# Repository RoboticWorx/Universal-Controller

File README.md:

# Universal_Controller
Files for my Universal Remote Controller project. 

***(Remember, you can download anything you'd like for yourself but you CAN'T sell or redistribute it. All my work is licensed, thanks!)***

Be sure to go to www.roboticworx.io for detailed tutorials on a variety of projects! Thanks for reading and happy making!

Best regards, 
Justin

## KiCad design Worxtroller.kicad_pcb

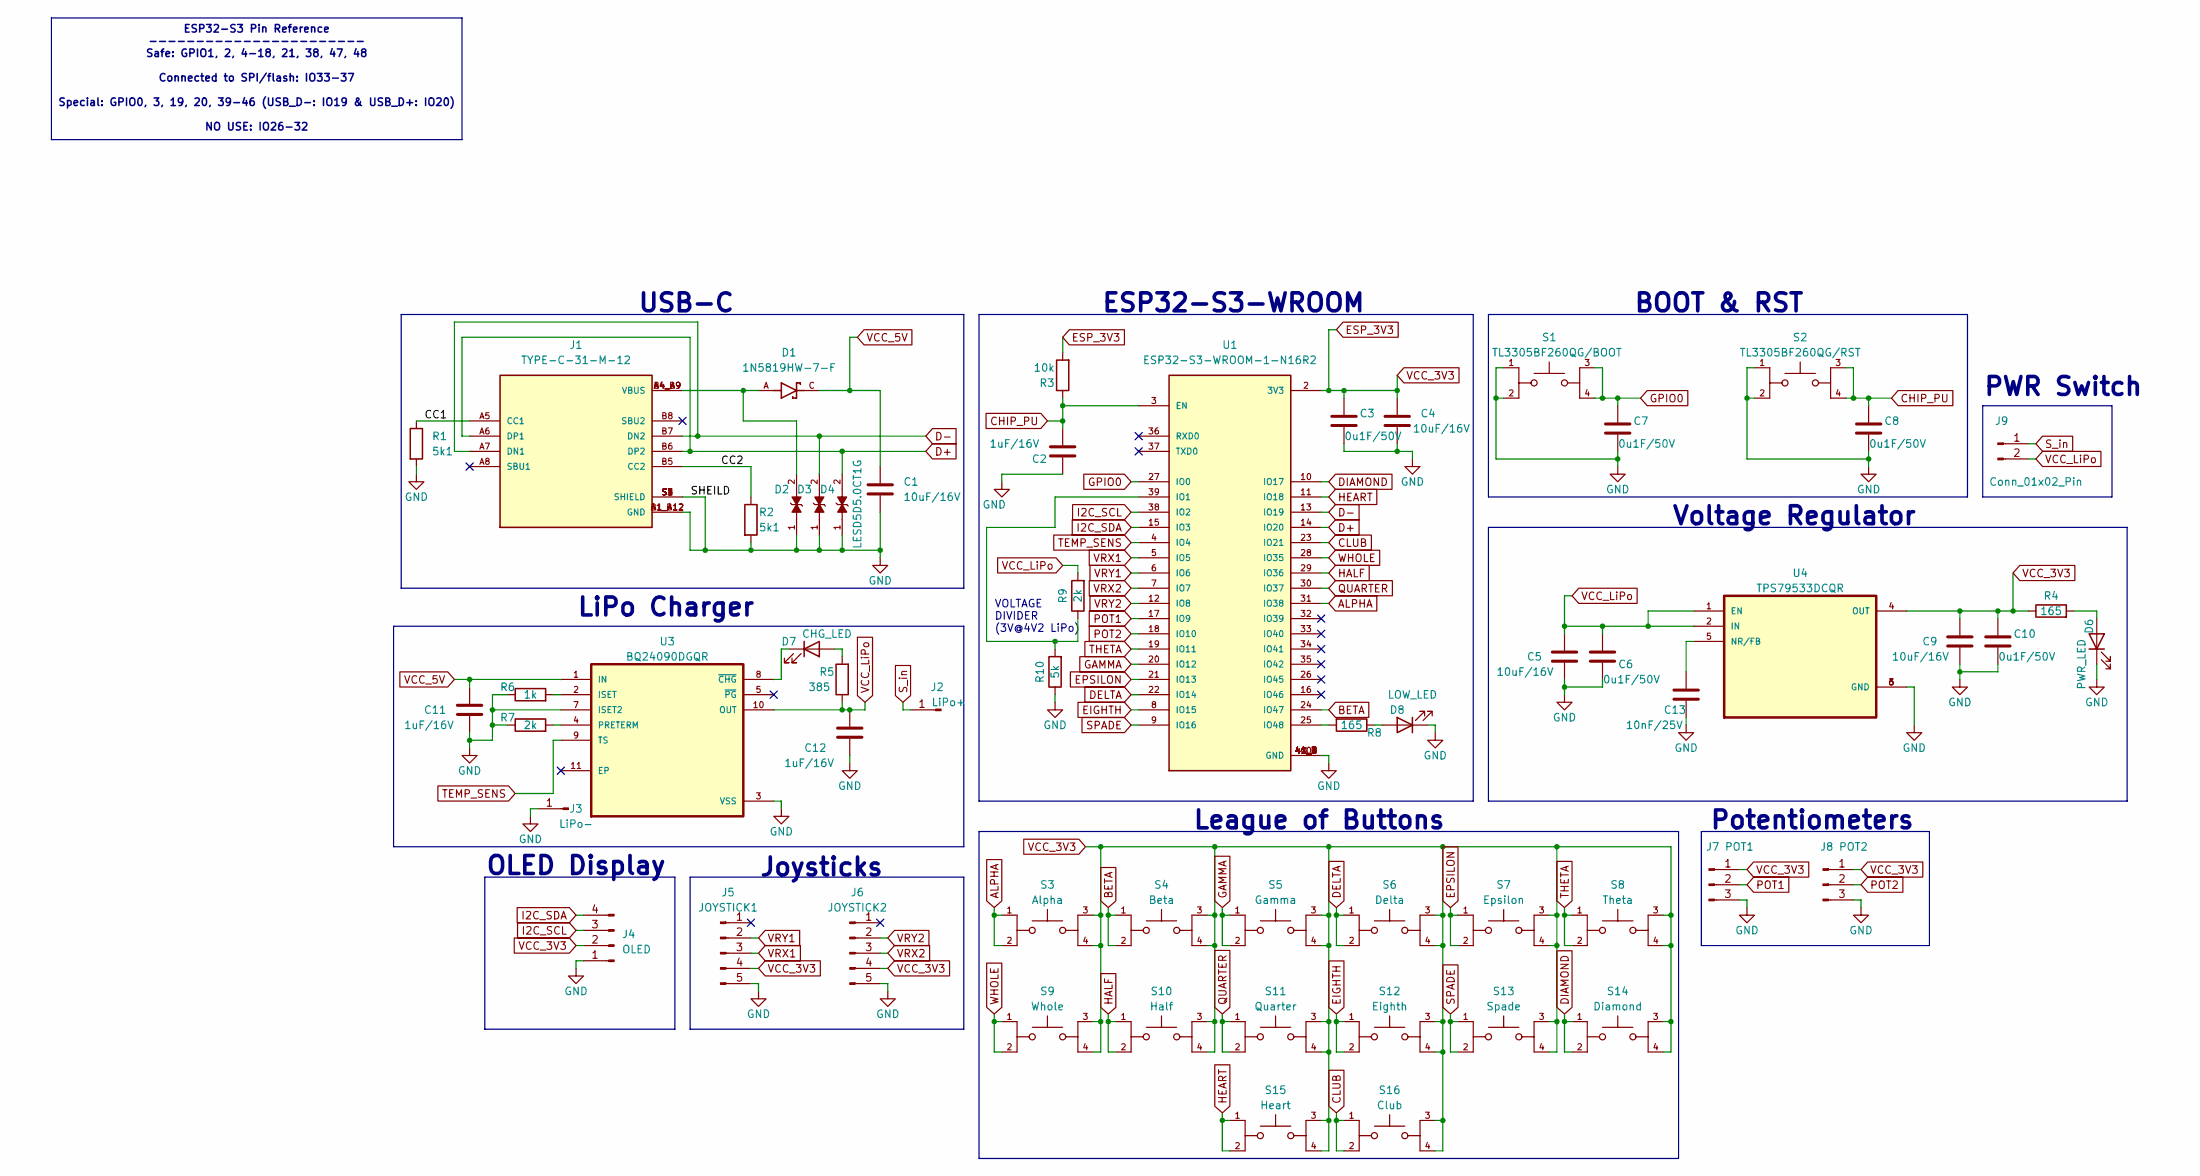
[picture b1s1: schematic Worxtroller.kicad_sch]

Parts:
C1, C4, C5, C9: 10uF/16V; C_0805_2012Metric_Pad1.18x1.45mm_HandSolder
C2, C11, C12: 1uF/16V; C_0603_1608Metric_Pad1.08x0.95mm_HandSolder
C3, C6, C7, C8, C10: 0u1F/50V; C_0201_0603Metric_Pad0.64x0.40mm_HandSolder
C13: 10nF/25V; C_0201_0603Metric_Pad0.64x0.40mm_HandSolder
D1: 1N5819HW-7-F; SOD3715X145N; PARTREV 18-2
D2, D3, D4: LESD5D5.0CT1G; TVS_LESD5D5.0CT1G; PARTREV O
D6: PWR_LED; LED_D3.0mm
D7: CHG_LED; LED_D3.0mm
D8: LOW_LED; LED_D3.0mm
J1: TYPE-C-31-M-12; HRO_TYPE-C-31-M-12; PARTREV 2020.12.08
J2: LiPo+; PinHeader_1x01_P2.54mm_Vertical
J3: LiPo-; PinHeader_1x01_P2.54mm_Vertical
J4: OLED; PinHeader_1x04_P2.54mm_Vertical
J5: JOYSTICK1; PinHeader_1x05_P2.54mm_Vertical
J6: JOYSTICK2; PinHeader_1x05_P2.54mm_Vertical
J7: POT1; PinHeader_1x03_P2.54mm_Vertical
J8: POT2; PinHeader_1x03_P2.54mm_Vertical
J9: Conn_01x02_Pin; PinHeader_1x02_P2.54mm_Vertical
R1, R2: 5k1; R_0805_2012Metric_Pad1.20x1.40mm_HandSolder
R3: 10k; R_0805_2012Metric_Pad1.20x1.40mm_HandSolder
R4, R8: 165; R_0603_1608Metric_Pad0.98x0.95mm_HandSolder
R5: 385; R_0603_1608Metric_Pad0.98x0.95mm_HandSolder
R6: 1k; R_0805_2012Metric_Pad1.20x1.40mm_HandSolder
R7, R9: 2k; R_0805_2012Metric_Pad1.20x1.40mm_HandSolder
R10: 5k; R_0805_2012Metric_Pad1.20x1.40mm_HandSolder
S1: TL3305BF260QG/BOOT; SW_TL3305BF260QG; PARTREV C
S2: TL3305BF260QG/RST; SW_TL3305BF260QG; PARTREV C
S3: Alpha; SW_TL3305BF260QG; PARTREV C
S4: Beta; SW_TL3305BF260QG; PARTREV C
S5: Gamma; SW_TL3305BF260QG; PARTREV C
S6: Delta; SW_TL3305BF260QG; PARTREV C
S7: Epsilon; SW_TL3305BF260QG; PARTREV C
S8: Theta; SW_TL3305BF260QG; PARTREV C
S9: Whole; SW_TL3305BF260QG; PARTREV C
S10: Half; SW_TL3305BF260QG; PARTREV C
S11: Quarter; SW_TL3305BF260QG; PARTREV C
S12: Eighth; SW_TL3305BF260QG; PARTREV C
S13: Spade; SW_TL3305BF260QG; PARTREV C
S14: Diamond; SW_TL3305BF260QG; PARTREV C
S15: Heart; SW_TL3305BF260QG; PARTREV C
S16: Club; SW_TL3305BF260QG; PARTREV C
U1: ESP32-S3-WROOM-1-N16R2; XCVR_ESP32-S3-WROOM-1-N16R2; PARTREV v1.0
U3: BQ24090DGQR; IC_XTR111AIDGQR
U4: TPS79533DCQR; SOT127P706X180-6N

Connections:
/CC1: J1.A5 (CC1), R1.1
/CC2: J1.B5 (CC2), R2.1
ALPHA: S3.1, S3.2, U1.31 (IO38)
BETA: S4.1, S4.2, U1.24 (IO47)
CHIP_PU: C2.2, C8.1, R3.1, S2.3, S2.4, U1.3 (EN)
CLUB: S16.1, S16.2, U1.23 (IO21)
D+: D4.2, J1.A6 (DP1), J1.B6 (DP2), U1.14 (IO20)
D-: D3.2, J1.A7 (DN1), J1.B7 (DN2), U1.13 (IO19)
DELTA: S6.1, S6.2, U1.22 (IO14)
DIAMOND: S14.1, S14.2, U1.10 (IO17)
EIGHTH: S12.1, S12.2, U1.8 (IO15)
EPSILON: S7.1, S7.2, U1.21 (IO13)
ESP_3V3: C3.1, C4.1, C9.1, C10.1, J4.2, J5.4, J6.4, J7.1, J8.1, R3.2, R4.1, S3.3, S3.4, S4.3, S4.4, S5.3, S5.4, S6.3, S6.4, S7.3, S7.4, S8.3, S8.4, S9.3, S9.4, S10.3, S10.4, S11.3, S11.4, S12.3, S12.4, S13.3, S13.4, S14.3, S14.4, S15.3, S15.4, S16.3, S16.4, U1.2 (3V3), U4.4 (OUT)
GAMMA: S5.1, S5.2, U1.20 (IO12)
GPIO0: C7.1, S1.3, S1.4, U1.27 (IO0)
HALF: S10.1, S10.2, U1.29 (IO36)
HEART: S15.1, S15.2, U1.11 (IO18)
I2C_SCL: J4.3, U1.38 (IO2)
I2C_SDA: J4.4, U1.15 (IO3)
unnamed: D1.A, D2.2, J1.A4_B9 (VBUS), J1.B4_A9 (VBUS)
unnamed: D6.2 (A), R4.2
unnamed: D7.2 (A), R5.2
unnamed: D7.1 (K), U3.8 (~CHG)
unnamed: D8.2 (A), R8.1
unnamed: R9.1, R10.2, U1.39 (IO1)
unnamed: R8.2, U1.25 (IO48)
unnamed: R6.2, U3.2 (ISET)
unnamed: R7.2, U3.4 (PRETERM)
unnamed: C13.1, U4.5 (NR/FB)
POT1: J7.2, U1.17 (IO9)
POT2: J8.2, U1.18 (IO10)
QUARTER: S11.1, S11.2, U1.30 (IO37)
SENSE: U1.4 (IO4), U3.9 (TS)
SPADE: S13.1, S13.2, U1.9 (IO16)
S_in: J2.1, J9.1
TEMP_SENS: C1.2, C2.1, C3.2, C4.2, C5.2, C6.2, C7.2, C8.2, C9.2, C10.2, C11.1, C12.1, C13.2, D2.1, D3.1, D4.1, D6.1 (K), D8.1 (K), J1.A1_B12 (GND), J1.B1_A12 (GND), J1.S1 (SHIELD), J1.S2 (SHIELD), J1.S3 (SHIELD), J1.S4 (SHIELD), J3.1, J4.1, J5.5, J6.5, J7.3, J8.3, R1.2, R2.2, R6.1, R7.1, R10.1, S1.1, S1.2, S2.1, S2.2, U1.1 (GND), U1.40 (GND), U1.41_1 (GND), U1.41_2 (GND), U1.41_3 (GND), U1.41_4 (GND), U1.41_5 (GND), U1.41_6 (GND), U1.41_7 (GND), U1.41_8 (GND), U1.41_9 (GND), U1.41_10, U1.41_11, U1.41_12, U1.41_13, U1.41_14, U1.41_15, U1.41_16, U1.41_17, U1.41_18, U1.41_19, U1.41_20, U1.41_21, U3.3 (VSS), U3.7 (ISET2), U3.11 (EP), U3.12, U3.13, U3.14, U3.15, U3.16, U4.3 (GND), U4.6 (GND)
THETA: S8.1, S8.2, U1.19 (IO11)
VCC_5V: C1.1, C11.2, D1.C, U3.1 (IN)
VCC_LiPo: C5.1, C6.1, C12.2, J9.2, R5.1, R9.2, U3.10 (OUT), U4.1 (EN), U4.2 (IN)
VRX1: J5.3, U1.5 (IO5)
VRX2: J6.3, U1.7 (IO7)
VRY1: J5.2, U1.6 (IO6)
VRY2: J6.2, U1.12 (IO8)
WHOLE: S9.1, S9.2, U1.28 (IO35)

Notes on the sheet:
ESP32-S3 Pin Reference ----------------------- Safe: GPIO1, 2, 4-18, 21, 38, 47, 48 Connected to SPI/flash: IO33-37 Special: GPIO0, 3, 19, 20, 39-46 (USB_D-: IO19 & USB_D+: IO20) NO USE: IO26-32
ESP32-S3-WROOM
OLED Display
Voltage Regulator
LiPo Charger
Joysticks
BOOT & RST
Potentiometers
VOLTAGE DIVIDER (3V@4V2 LiPo)
League of Buttons
PWR Switch
USB-C

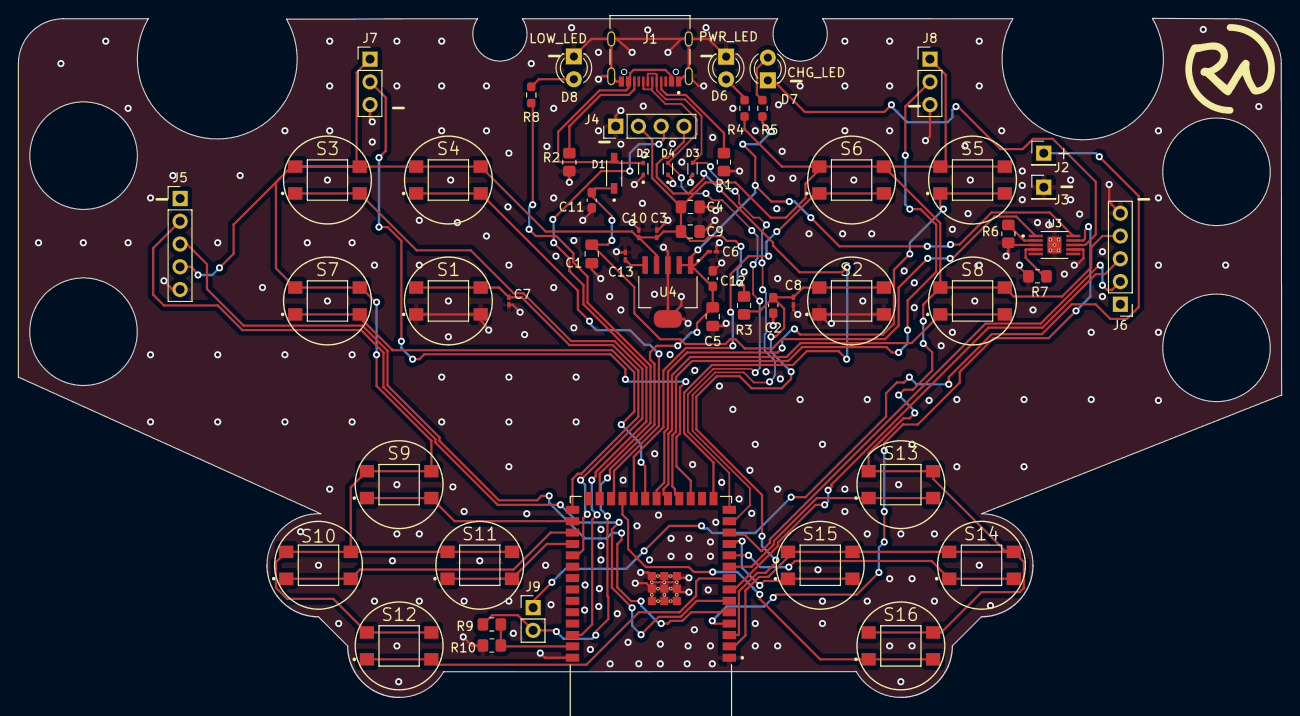
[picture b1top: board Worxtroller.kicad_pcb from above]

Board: 2 copper layers, 141.0 x 75.8 mm, 58 parts (0 on the bottom side), 44 nets.

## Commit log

2023-09-04 Electrical Schematic Image
2023-09-04 Reference Sheet
2023-09-04 Part List
2023-09-05 Part List (BOM)
2023-09-05 Gerber File for PCB Fabrication
2023-09-05 Editable KiCad files
2023-09-05 Universal Controller Code (Transmitter)
2023-09-05 Update Universal Controller Code (Transmitter)
2023-09-05 Universal_Controller_Reciever_Example
2023-09-05 Rename Universal_Controller_Reciever_Example to Universal Controller Receiver Example
2023-09-05 Create Universal Controller Receiver Example
2023-09-06 Universal Controller Fabrication File (GERBER)
2023-09-06 U.C. Editable KiCad Files
